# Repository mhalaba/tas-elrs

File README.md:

# TAS-ELRS

**Hardened ExpressLRS 4.1.0 fork** — ChaCha20 RC payloads, keyed MAC, anti-replay, jam classification to the flight controller, deterministic FHSS prune, months-long RX standby with a keyed wake token.

- **Start here:** [TAS_README.md](TAS_README.md) (PL) · [English](docs/TAS_README_EN.md) · [Українська](docs/TAS_README_UK.md)
- **Build:** uncomment `-DTAS_HARDENING` in `src/user_defines.txt` (TX **and** RX together). Stock ELRS will not talk to a hardened build.
- **Tests:** `bash src/test/run_tas_tests.sh` (alias: `run_mil_tests.sh`)
- **Hardware:** [`hardware/`](hardware/README.md) — TAS-RX-900-C3
- **License:** GPL-3.0 (fork as a whole) · TAS originals also MIT — see `NOTICE`

Current TAS release: **v2.2** (epoch-0 key + jam-classifier security patch).

The remainder of this file is the upstream ExpressLRS README, retained for attribution.

---

<center>

</center>

**ExpressLRS** is developed and maintained by **ExpressLRS LLC** and its passionate open source community, working together to advance reliable, high-performance radio control technology.

## Support ExpressLRS
You can support ExpressLRS by contributing code, testing new features, sharing your ideas, or helping others get started. We are exceptionally grateful for those who donate their time to our passion.

If you don't have time to lend a hand in that way but still want to have an impact, consider donating. Donations are used for infrastructure costs and to buy test equipment needed to further the project and make it securely accessible. ExpressLRS accepts donations through Open Collective, which provides recognition of donors and transparency on how that support is utilized.

We appreciate all forms of contribution and hope you will join us on Discord!

## Website
For general information on the project please refer to our guides on the [website](https://www.expresslrs.org/), and our [FAQ](https://www.expresslrs.org/faq/)

## About

ExpressLRS is an open source Radio Link for Radio Control applications. Designed to be the best FPV Racing link, it is based on the fantastic Semtech **SX127x**/**SX1280** LoRa hardware combined with an Espressif or STM32 Processor. Using LoRa modulation as well as reduced packet size it achieves best in class range and latency. It achieves this using a highly optimized over-the-air packet structure, giving simultaneous range and latency advantages. It supports both 900 MHz and 2.4 GHz links, each with their own benefits. 900 MHz supports a maximum of 200 Hz packet rate, with higher penetration. 2.4 GHz supports a blistering fast 1000 Hz on [EdgeTX](http://edgetx.org/). With hundreds of different hardware targets from a wide range of hardware manufacturers, the choice of hardware is constantly growing, with different hardware suited to different requirements.

## Configurator
To configure your ExpressLRS hardware, the ExpressLRS Configurator can be used, which is found here:

https://github.com/ExpressLRS/ExpressLRS-Configurator/releases/

## Community
We have both a [Discord Server](https://discord.gg/expresslrs) and [Facebook Group](https://www.facebook.com/groups/636441730280366), which have great support for new users and constant ongoing development discussion

## Features

ExpressLRS has the following features:

- Up to 1000 Hz Packet Rate
- Telemetry (Betaflight Lua Compatibility)
- Wifi Updates
- Bluetooth or WiFi Sim Joystick
- Oled & TFT Displays
- 2.4 GHz, 900 MHz, and Dual-Band RC Link
- SMD Antenna - allows for easier installation into micros
- Supported receiver protocols: CRSF, SBUS, SUMD, HoTT Telemetry, MAVLink, and PWM
- VTX and VRX Frequency adjustments from the Lua, including SmartAudio and Tramp support
- Bind Phrases - no need for button binding

with many more features on the way!

## Supported Hardware

ExpressLRS currently supports hardware from a wide range of manufacturers. In principle, the targets listed in the [ExpressLRS Configurator](https://github.com/ExpressLRS/ExpressLRS-Configurator/releases/) are tested and supported hardware.

See [Hardware Selection](https://www.expresslrs.org/hardware/hardware-selection/) for guidance. We do not manufacture any of our hardware, so we can only provide limited support for faulty hardware.

## Developers

If you are a developer and would like to contribute to the project, feel free to join the [discord](https://discord.gg/expresslrs) and chat about bugs and issues. You can also look for issues at the [GitHub Issue Tracker](https://github.com/ExpressLRS/ExpressLRS/issues). The best thing to do is to submit a Pull Request to the GitHub Repository.

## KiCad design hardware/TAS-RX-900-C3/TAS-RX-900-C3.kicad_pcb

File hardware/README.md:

# TAS-ELRS — Hardware

> **Wersje:** [English](README_EN.md) · [Українська](README_UK.md) · [Español](README_ES.md) · [Português](README_PT.md) · [العربية](README_AR.md)

Referencyjna elektronika dla targetów firmware z tego forka.

## TAS-RX-900-C3 (gotowe v1.0)

RX 868/915 MHz: ESP32-C3 + E28-900M22S (SX1276). Zgodny z targetem
`Unified_ESP32C3_900_RX_via_UART` — **zero zmian w firmware**.

- `TAS-RX-900-C3/TAS-RX-900-C3.kicad_sch` — schemat (KiCad 8)
- `TAS-RX-900-C3/TAS-RX-900-C3.kicad_pcb` — szkielet PCB 25×35 mm (outline, footprints, GND zone; routing przed produkcją!)
- `TAS-RX-900-C3/PINOUT.md` — pinout + zasady layoutu RF
- `TAS-RX-900-C3/BOM.csv` — materiałówka (~12 pozycji)
- `../src/hardware/RX/TAS RX 900 C3.json` — hardware-def do flashowania unified targetu przez Configurator

## Procedura uruchomienia

1. Wytwórz PCB wg PINOUT.md (po ręcznym routingu i DRC!).
2. Zmontuj BOM; podłącz antenę PRZED pierwszym załączeniem (PA bez anteny = śmierć SX1276).
3. Flash: Configurator → custom target → wczytaj JSON `TAS RX 900 C3.json` → firmware `Unified_ESP32C3_900_RX_via_UART` z `-DTAS_HARDENING`.
4. Bench test failsafe + range test wg sekcji 7 TAS_README.

## Zasady projektu sprzętu

- Części ≥2 niezależnych źródeł (L4 z README głównego).
- Antena zawsze przed włączeniem; moc zgodna z prawem regionu.
- Każda rewizja PCB = osobny katalog `TAS-RX-900-C3-revB/` itd., nigdy nadpisywanie.

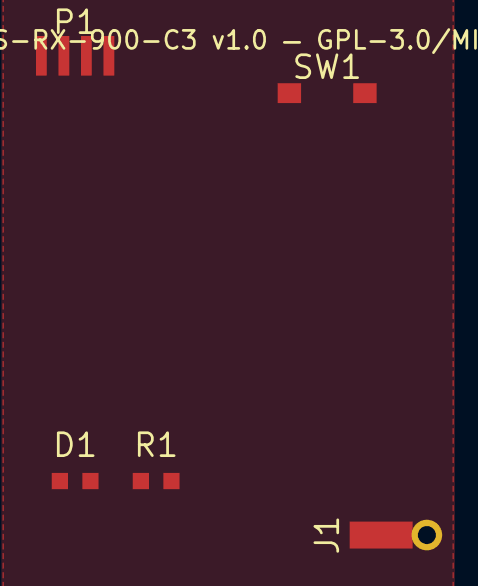
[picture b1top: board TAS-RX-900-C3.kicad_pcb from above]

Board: 2 copper layers, 5 parts (0 on the bottom side), 2 nets, no tracks yet.

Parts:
D1: LED_G; LED_0603_1608Metric
J1: ANT_SMA; SMA_EDGE_MOUNT
P1: CRSF_JST-GH; JST_GH_BM04B-GHS-TBT_1x04-1MP_P1.25mm_Horizontal
R1: 1k; R_0603_1608Metric
SW1: BIND_BTN; SW_SPST_PTS645

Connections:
GND: J1.2, P1.4, SW1.2
LED_K: D1.1, R1.2

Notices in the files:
hardware/TAS-RX-900-C3/TAS-RX-900-C3.kicad_pcb:
TAS-RX-900-C3 v1.0 — GPL-3.0/MIT
